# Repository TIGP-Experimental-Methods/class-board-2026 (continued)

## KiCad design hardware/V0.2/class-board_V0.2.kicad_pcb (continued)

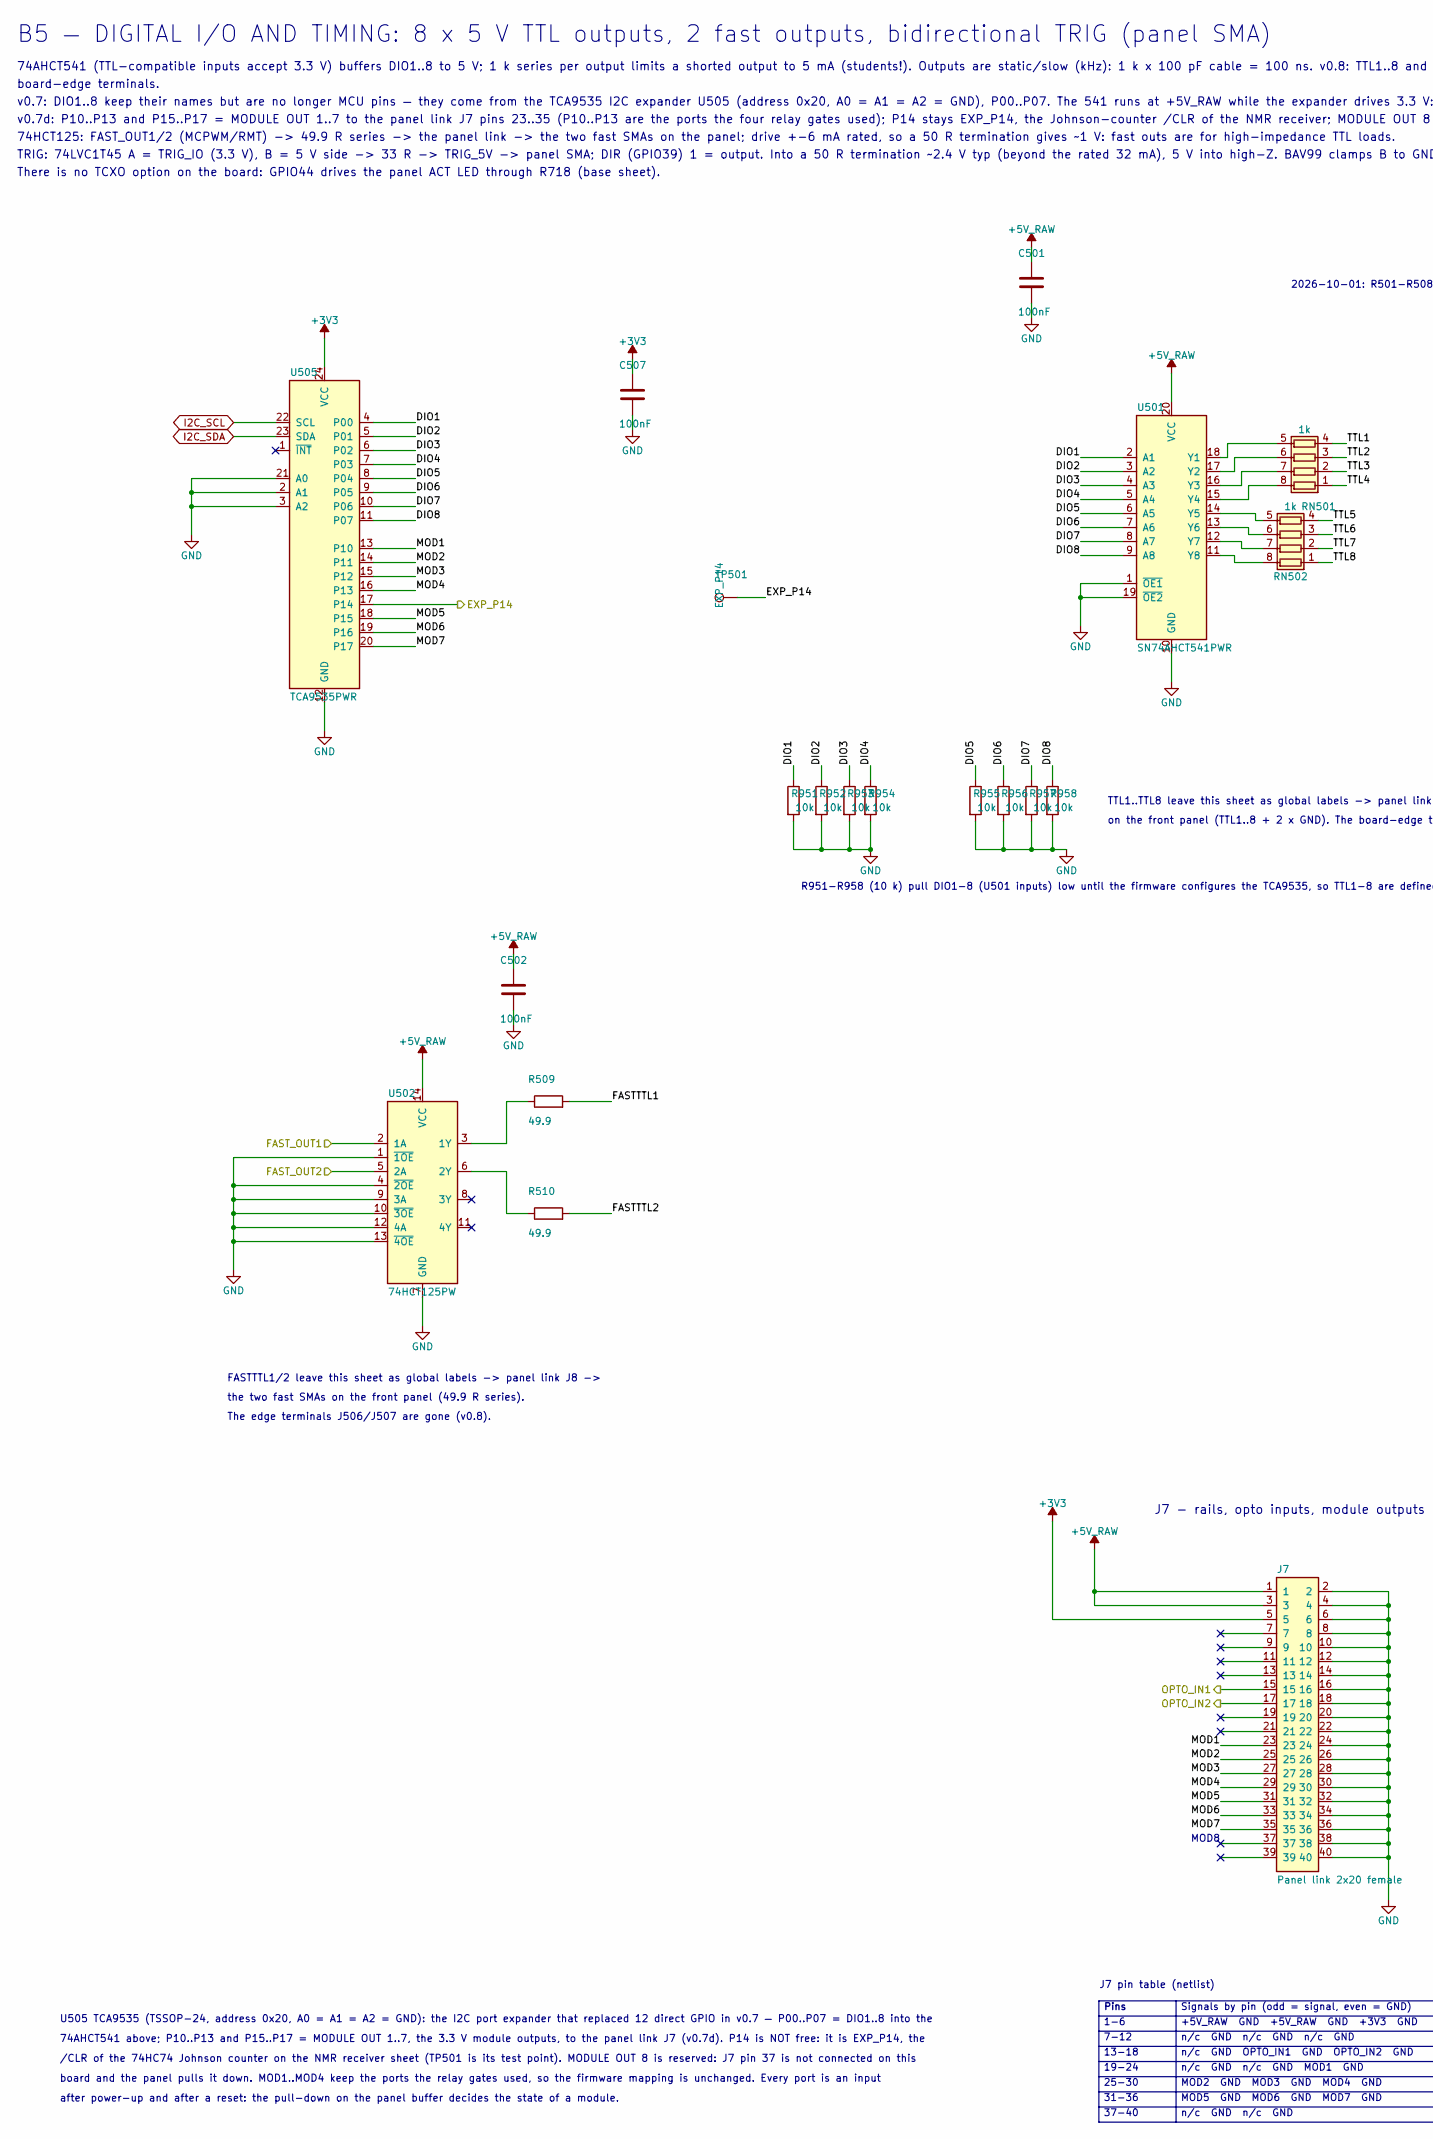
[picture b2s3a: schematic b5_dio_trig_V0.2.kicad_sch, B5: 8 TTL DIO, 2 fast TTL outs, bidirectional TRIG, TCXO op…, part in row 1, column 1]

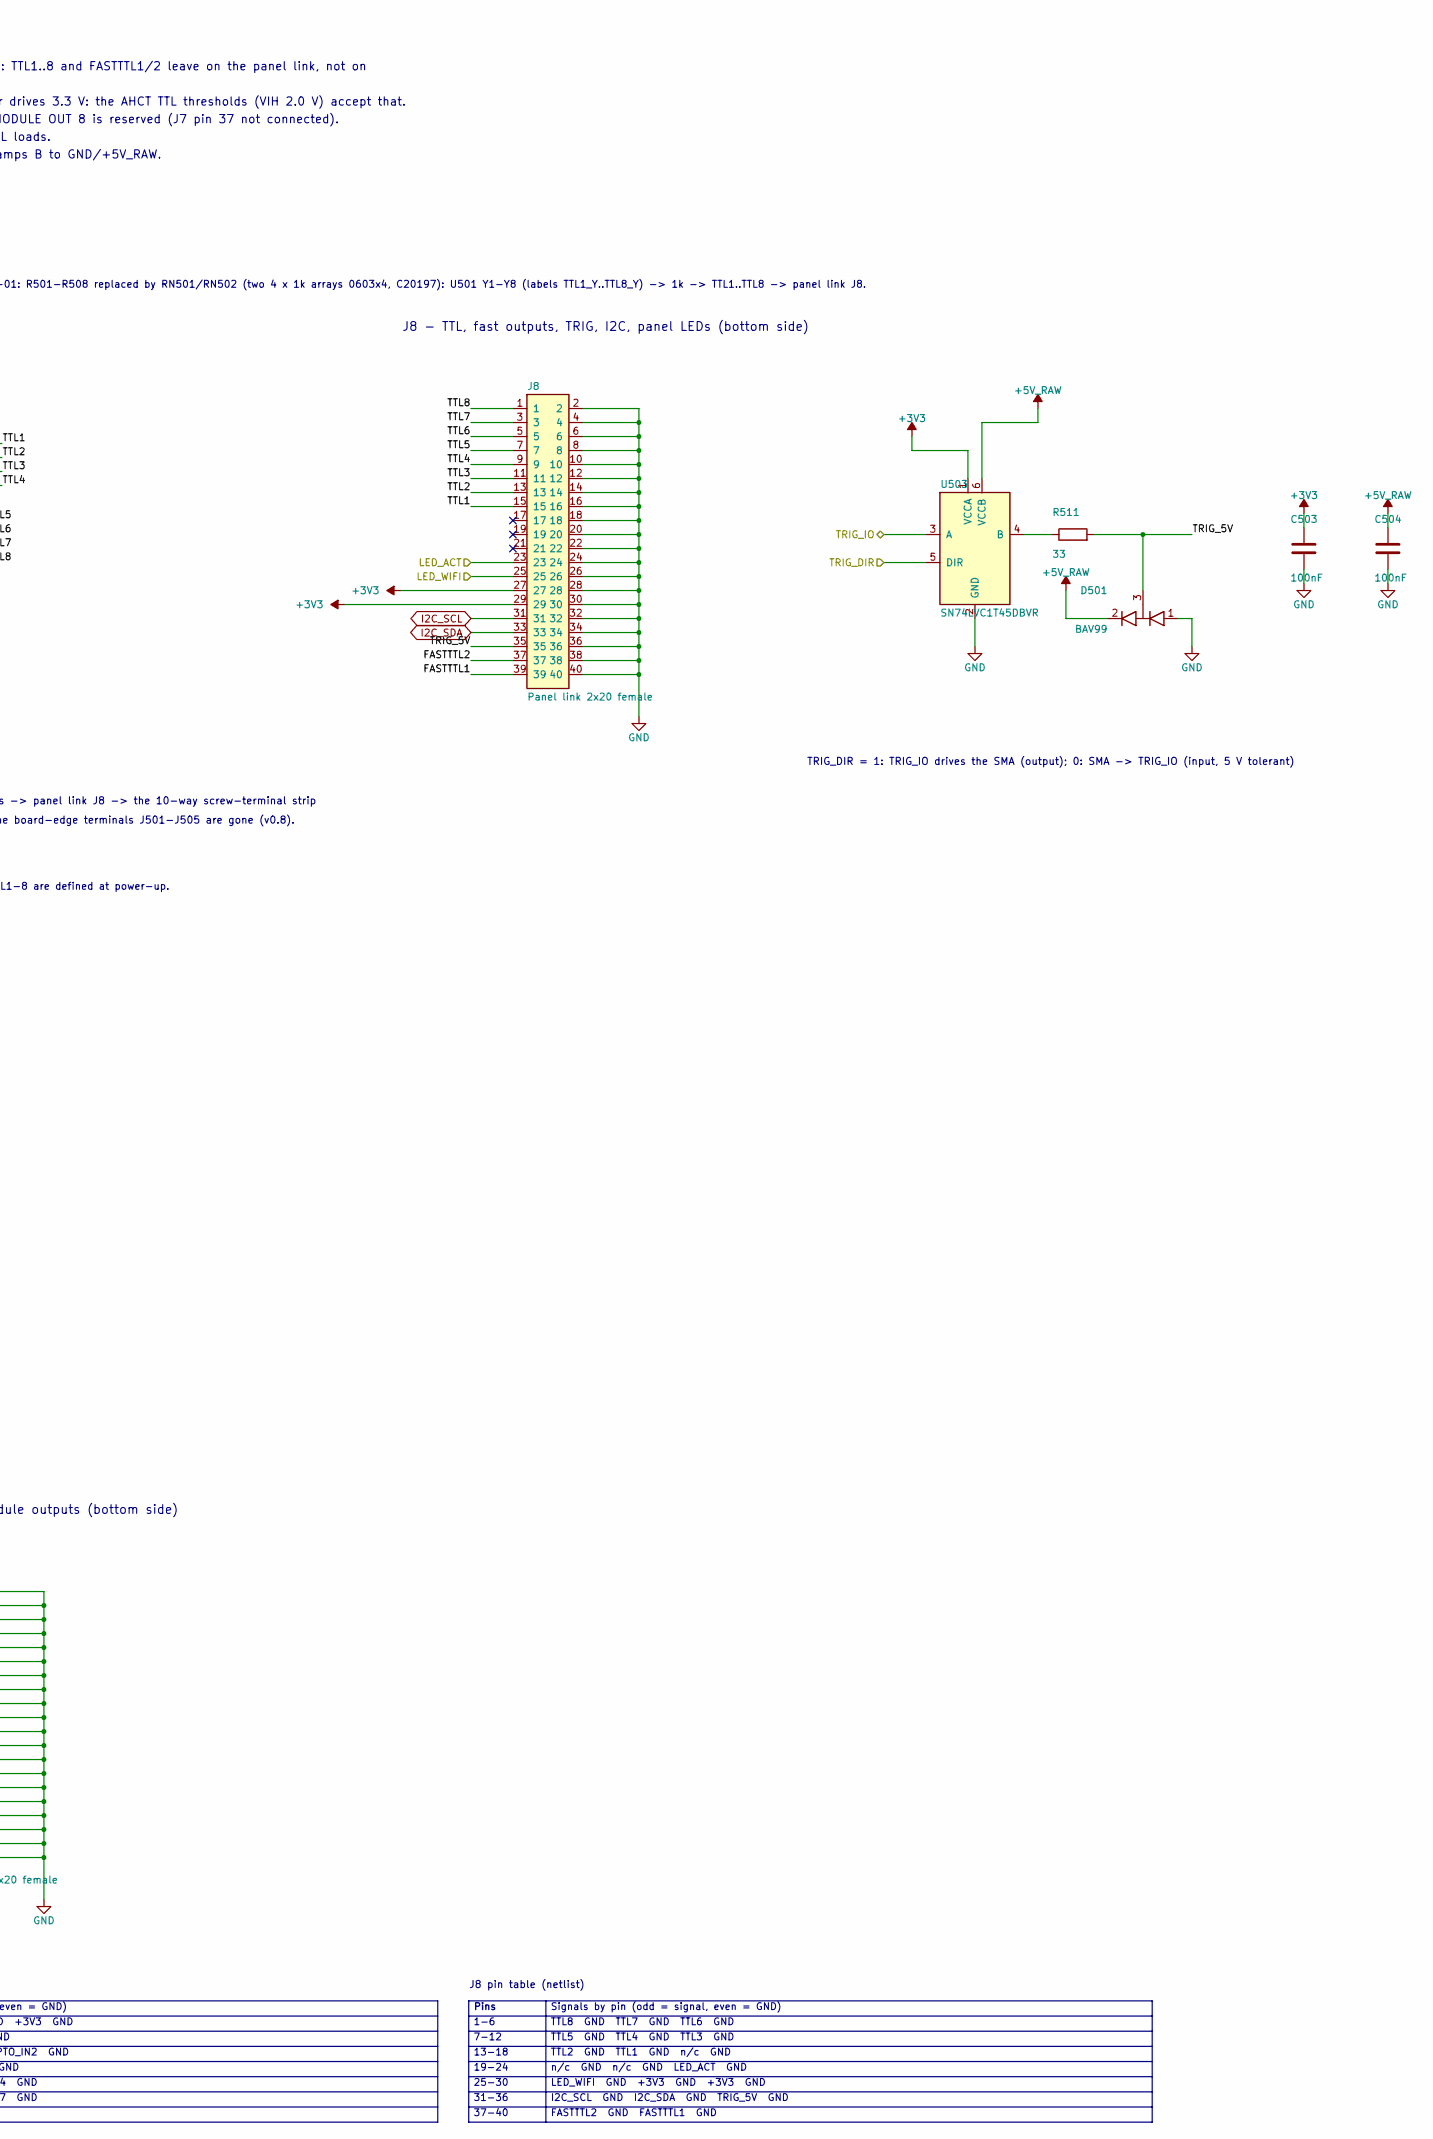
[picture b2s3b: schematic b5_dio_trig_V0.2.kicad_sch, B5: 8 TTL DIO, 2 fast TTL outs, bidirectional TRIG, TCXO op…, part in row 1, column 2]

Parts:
C501, C502, C503, C504, C507: 100nF; C_0603_1608Metric; MPN CC0603KRX7R9BB104; LCSC C14663
D501: BAV99; SOT-23-3_L2.9-W1.6-P1.90-LS2.8-BR; MPN BAV99,215; LCSC C2500
J7, J8: Panel link 2x20 female; PinSocket_2x20_P2.54mm_Vertical; MPN 2.54-2*20P (8.5 mm); LCSC C5124634
R509, R510: 49.9; R_0603_1608Metric; MPN 0603WAF499JT5E; LCSC C23185
R511: 33; R_0603_1608Metric; MPN 0603WAF330JT5E; LCSC C23140
R951, R952, R953, R954, R955, R956, R957, R958: 10k; R_0603_1608Metric; LCSC C25804
RN501, RN502: 1k; R_Array_Convex_4x0603; LCSC C20197
TP501: EXP_P14; TestPoint_Pad_D1.5mm
U501: SN74AHCT541PWR; TSSOP-20_L6.5-W4.4-P0.65-LS6.4-BL; MPN SN74AHCT541PWR; LCSC C50989
U502: 74HCT125PW; TSSOP-14_L5.0-W4.4-P0.65-LS6.4-BL; MPN 74HCT125PW,118; LCSC C131316
U503: SN74LVC1T45DBVR; SOT-23-6_L2.9-W1.6-P0.95-LS2.8-BR; MPN SN74LVC1T45DBVR; LCSC C7843
U505: TCA9535PWR; TSSOP-24_L7.8-W4.4-P0.65-LS6.4-BL; MPN TCA9535PWR; LCSC C22396388

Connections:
+3V3: C503.1, C507.1, J7.5, J8.27, J8.29, U503.1 (VCCA), U505.24 (VCC); also elsewhere on the board
/b5_dio_trig/DIO1: R951.1, U501.2 (A1), U505.4 (P00)
/b5_dio_trig/DIO2: R952.1, U501.3 (A2), U505.5 (P01)
/b5_dio_trig/DIO3: R953.1, U501.4 (A3), U505.6 (P02)
/b5_dio_trig/DIO4: R954.1, U501.5 (A4), U505.7 (P03)
/b5_dio_trig/DIO5: R955.1, U501.6 (A5), U505.8 (P04)
/b5_dio_trig/DIO6: R956.1, U501.7 (A6), U505.9 (P05)
/b5_dio_trig/DIO7: R957.1, U501.8 (A7), U505.10 (P06)
/b5_dio_trig/DIO8: R958.1, U501.9 (A8), U505.11 (P07)
/b5_dio_trig/EXP_P14: TP501.1 (1_1), U505.17 (P14); also elsewhere on the board
/b5_dio_trig/FASTTTL1: J8.39, R509.2
/b5_dio_trig/FASTTTL2: J8.37, R510.2
/b5_dio_trig/FAST_OUT1: U502.2 (1A); also elsewhere on the board
/b5_dio_trig/FAST_OUT2: U502.5 (2A); also elsewhere on the board
/b5_dio_trig/LED_ACT: J8.23; also elsewhere on the board
/b5_dio_trig/LED_WIFI: J8.25; also elsewhere on the board
/b5_dio_trig/MOD1: J7.23, U505.13 (P10)
/b5_dio_trig/MOD2: J7.25, U505.14 (P11)
/b5_dio_trig/MOD3: J7.27, U505.15 (P12)
/b5_dio_trig/MOD4: J7.29, U505.16 (P13)
/b5_dio_trig/MOD5: J7.31, U505.18 (P15)
/b5_dio_trig/MOD6: J7.33, U505.19 (P16)
/b5_dio_trig/MOD7: J7.35, U505.20 (P17)
/b5_dio_trig/OPTO_IN1: J7.15; also elsewhere on the board
/b5_dio_trig/OPTO_IN2: J7.17; also elsewhere on the board
/b5_dio_trig/TRIG_5V: D501.3 (COM), J8.35, R511.2
/b5_dio_trig/TRIG_DIR: U503.5 (DIR); also elsewhere on the board
/b5_dio_trig/TRIG_IO: U503.3 (A); also elsewhere on the board
/b5_dio_trig/TTL1: J8.15, RN501.4 (R4.1)
/b5_dio_trig/TTL2: J8.13, RN501.3 (R3.1)
/b5_dio_trig/TTL3: J8.11, RN501.2 (R2.1)
/b5_dio_trig/TTL4: J8.9, RN501.1 (R1.1)
/b5_dio_trig/TTL5: J8.7, RN502.4 (R4.1)
/b5_dio_trig/TTL6: J8.5, RN502.3 (R3.1)
/b5_dio_trig/TTL7: J8.3, RN502.2 (R2.1)
/b5_dio_trig/TTL8: J8.1, RN502.1 (R1.1)
GND: C501.2, C502.2, C503.2, C504.2, C507.2, D501.1 (A1), J7.2, J7.4, J7.6, J7.8, J7.10, J7.12, J7.14, J7.16, J7.18, J7.20, J7.22, J7.24, J7.26, J7.28, J7.30, J7.32, J7.34, J7.36, J7.38, J7.40, J8.2, J8.4, J8.6, J8.8, J8.10, J8.12, J8.14, J8.16, J8.18, J8.20, J8.22, J8.24, J8.26, J8.28, J8.30, J8.32, J8.34, J8.36, J8.38, J8.40, R951.2, R952.2, R953.2, R954.2, R955.2, R956.2, R957.2, R958.2, U501.1 (~OE1), U501.10 (GND), U501.19 (~OE2), U502.1 (~1OE), U502.4 (~2OE), U502.7 (GND), U502.9 (3A), U502.10 (~3OE), U502.12 (4A), U502.13 (~4OE), U503.2 (GND), U505.2 (A1), U505.3 (A2), U505.12 (GND), U505.21 (A0); also elsewhere on the board
I2C_SCL: J8.31, U505.22 (SCL); also elsewhere on the board
I2C_SDA: J8.33, U505.23 (SDA); also elsewhere on the board
unnamed: RN501.8 (R1.2), U501.15 (Y4)
unnamed: RN501.7 (R2.2), U501.16 (Y3)
unnamed: RN501.6 (R3.2), U501.17 (Y2)
unnamed: RN501.5 (R4.2), U501.18 (Y1)
unnamed: RN502.8 (R1.2), U501.11 (Y8)
unnamed: RN502.7 (R2.2), U501.12 (Y7)
unnamed: RN502.6 (R3.2), U501.13 (Y6)
unnamed: RN502.5 (R4.2), U501.14 (Y5)
unnamed: R509.1, U502.3 (1Y)
unnamed: R510.1, U502.6 (2Y)
unnamed: R511.1, U503.4 (B)

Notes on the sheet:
U505 TCA9535 (TSSOP-24, address 0x20, A0 = A1 = A2 = GND): the I2C port expander that replaced 12 direct GPIO in v0.7 — P00..P07 = DIO1..8 into the
v0.7: DIO1..8 keep their names but are no longer MCU pins — they come from the TCA9535 I2C expander U505 (address 0x20, A0 = A1 = A2 = GND), P00..P07. The 541 runs at +5V_RAW while the expander drives 3.3 V: the AHCT TTL thresholds (VIH 2.0 V) accept that.
after power-up and after a reset: the pull-down on the panel buffer decides the state of a module.
Pins
board-edge terminals.
25-30
2026-10-01: R501-R508 replaced by RN501/RN502 (two 4 x 1k arrays 0603x4, C20197): U501 Y1-Y8 (labels TTL1_Y..TTL8_Y) -> 1k -> TTL1..TTL8 -> panel link J8.
1-6
The edge terminals J506/J507 are gone (v0.8).
19-24
13-18
74HCT125: FAST_OUT1/2 (MCPWM/RMT) -> 49.9 R series -> the panel link -> the two fast SMAs on the panel; drive +-6 mA rated, so a 50 R termination gives ~1 V: fast outs are for high-impedance TTL loads.
TRIG: 74LVC1T45 A = TRIG_IO (3.3 V), B = 5 V side -> 33 R -> TRIG_5V -> panel SMA; DIR (GPIO39) 1 = output. Into a 50 R termination ~2.4 V typ (beyond the rated 32 mA), 5 V into high-Z. BAV99 clamps B to GND/+5V_RAW.
the two fast SMAs on the front panel (49.9 R series).
7-12
board and the panel pulls it down. MOD1..MOD4 keep the ports the relay gates used, so the firmware mapping is unchanged. Every port is an input
MOD8
on the front panel (TTL1..8 + 2 x GND). The board-edge terminals J501-J505 are gone (v0.8).
TRIG_DIR = 1: TRIG_IO drives the SMA (output); 0: SMA -> TRIG_IO (input, 5 V tolerant)
31-36
74AHCT541 (TTL-compatible inputs accept 3.3 V) buffers DIO1..8 to 5 V; 1 k series per output limits a shorted output to 5 mA (students!). Outputs are static/slow (kHz): 1 k x 100 pF cable = 100 ns. v0.8: TTL1..8 and FASTTTL1/2 leave on the panel link, not on
37-40
J7 pin table (netlist)
Signals by pin (odd = signal, even = GND)
+5V_RAW GND +5V_RAW GND +3V3 GND
n/c GND n/c GND n/c GND
n/c GND OPTO_IN1 GND OPTO_IN2 GND
n/c GND n/c GND MOD1 GND
MOD2 GND MOD3 GND MOD4 GND
MOD5 GND MOD6 GND MOD7 GND
n/c GND n/c GND
J8 pin table (netlist)
TTL8 GND TTL7 GND TTL6 GND
TTL5 GND TTL4 GND TTL3 GND
TTL2 GND TTL1 GND n/c GND
n/c GND n/c GND LED_ACT GND
LED_WIFI GND +3V3 GND +3V3 GND
I2C_SCL GND I2C_SDA GND TRIG_5V GND
FASTTTL2 GND FASTTTL1 GND
J7 - rails, opto inputs, module outputs (bottom side)

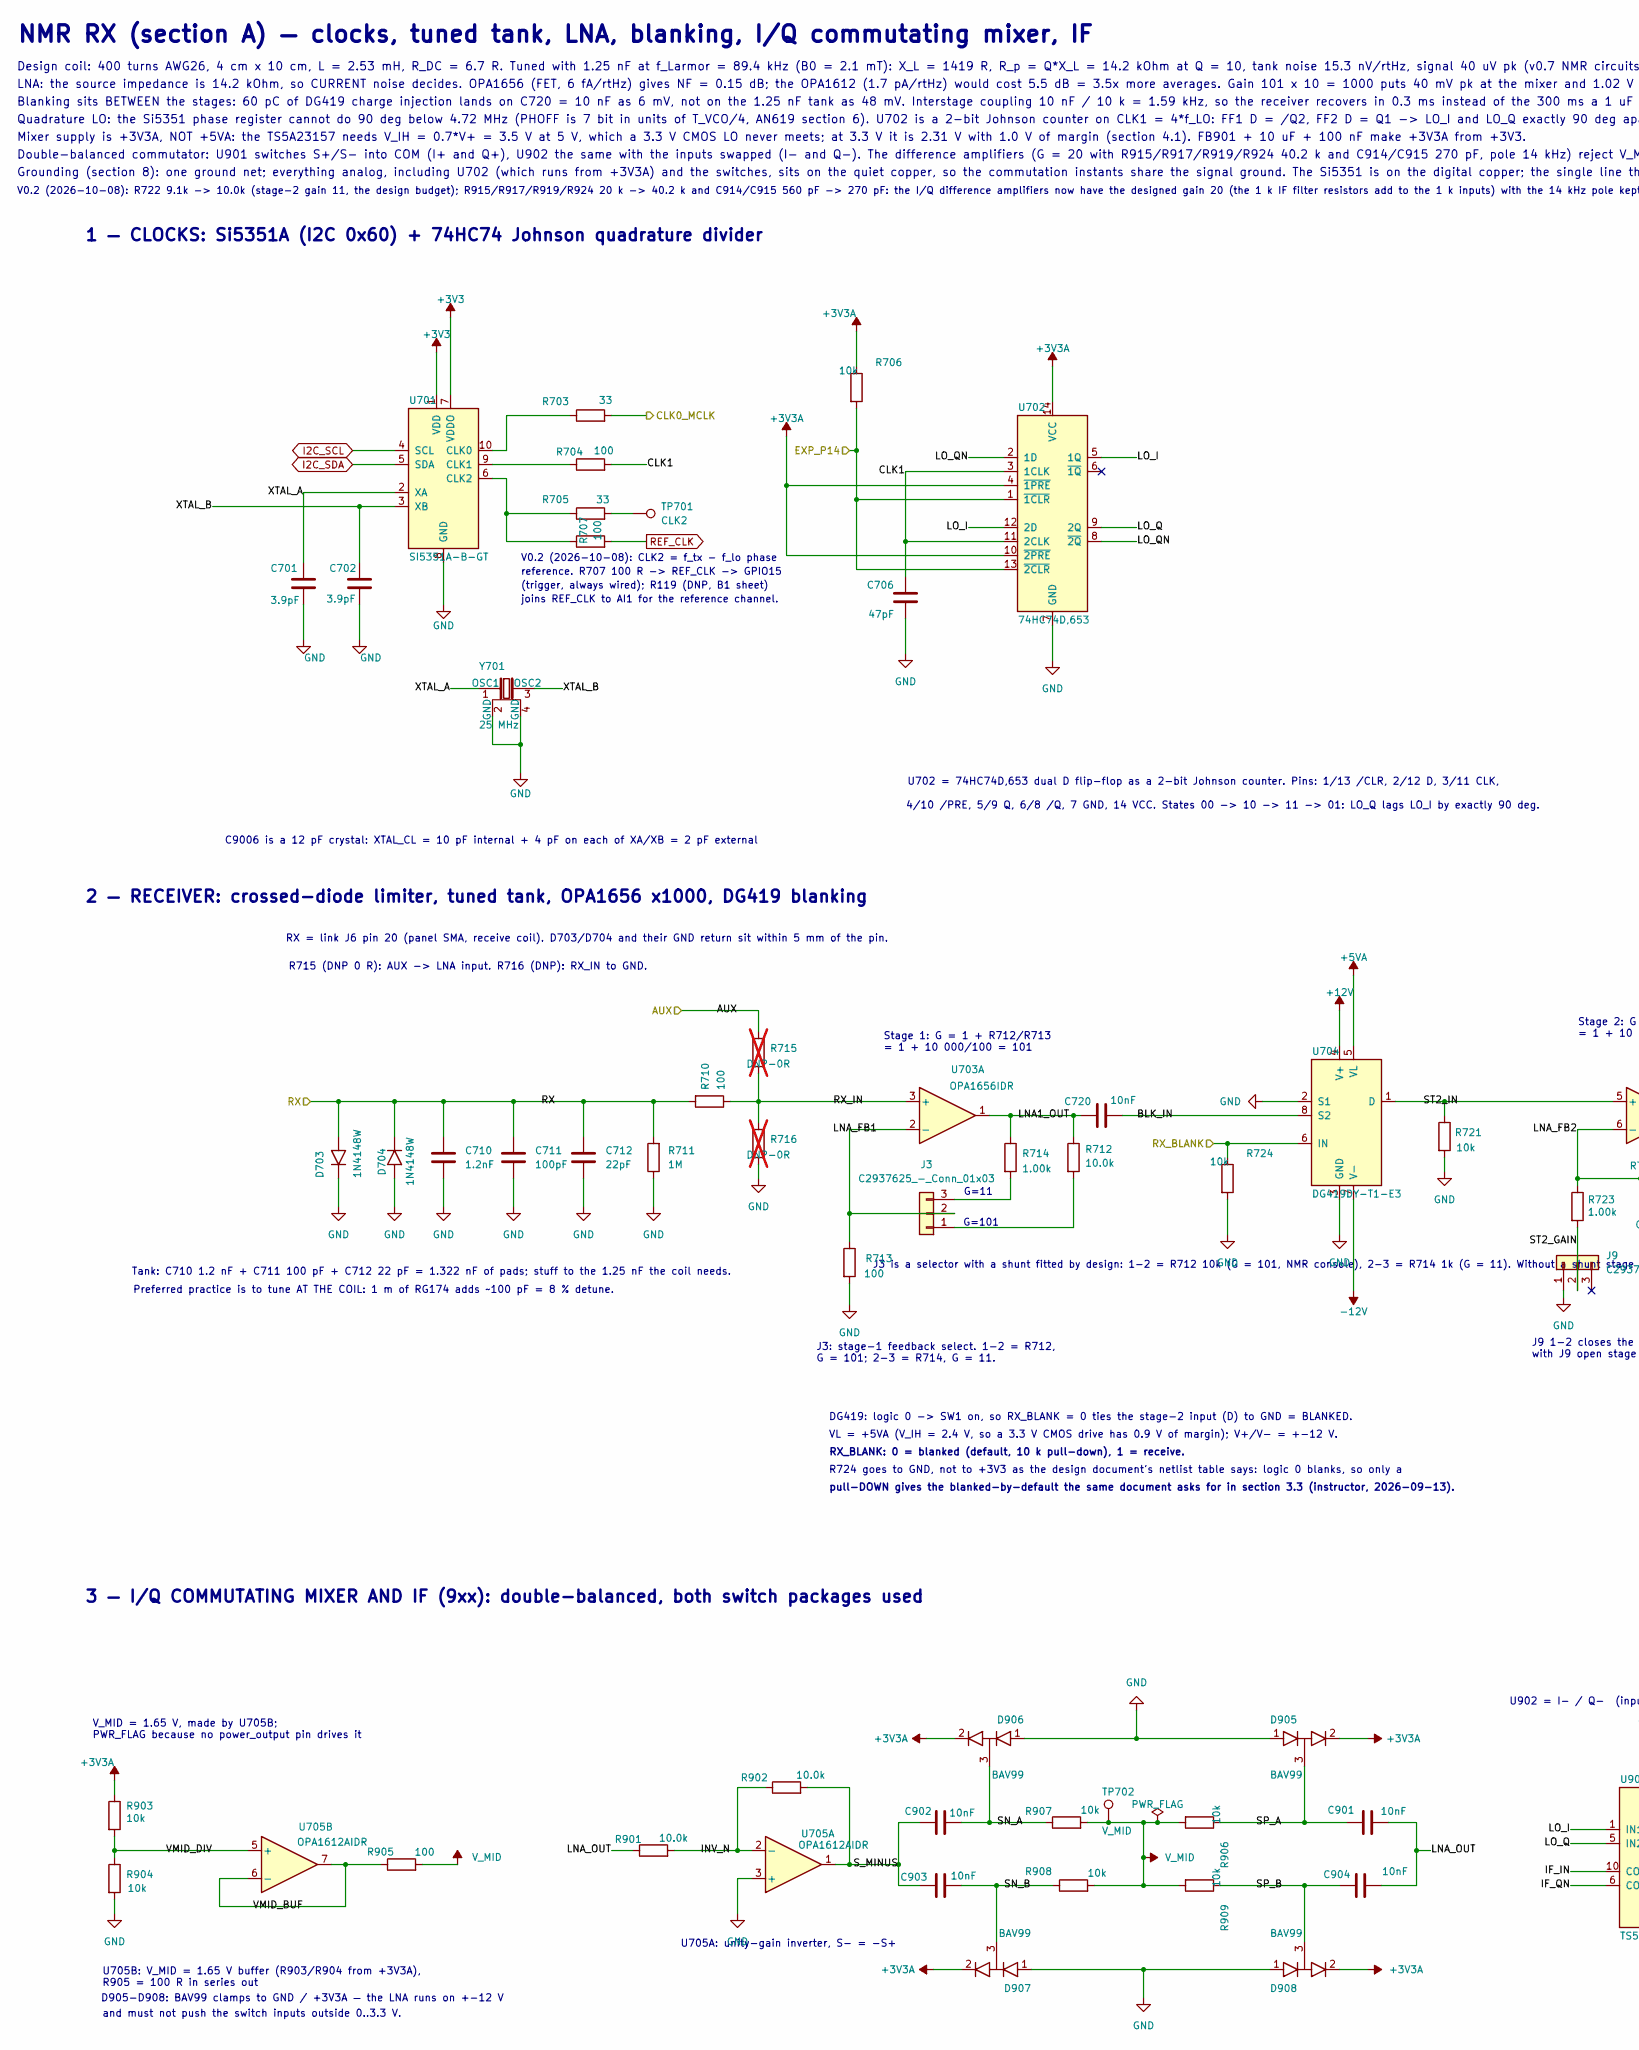
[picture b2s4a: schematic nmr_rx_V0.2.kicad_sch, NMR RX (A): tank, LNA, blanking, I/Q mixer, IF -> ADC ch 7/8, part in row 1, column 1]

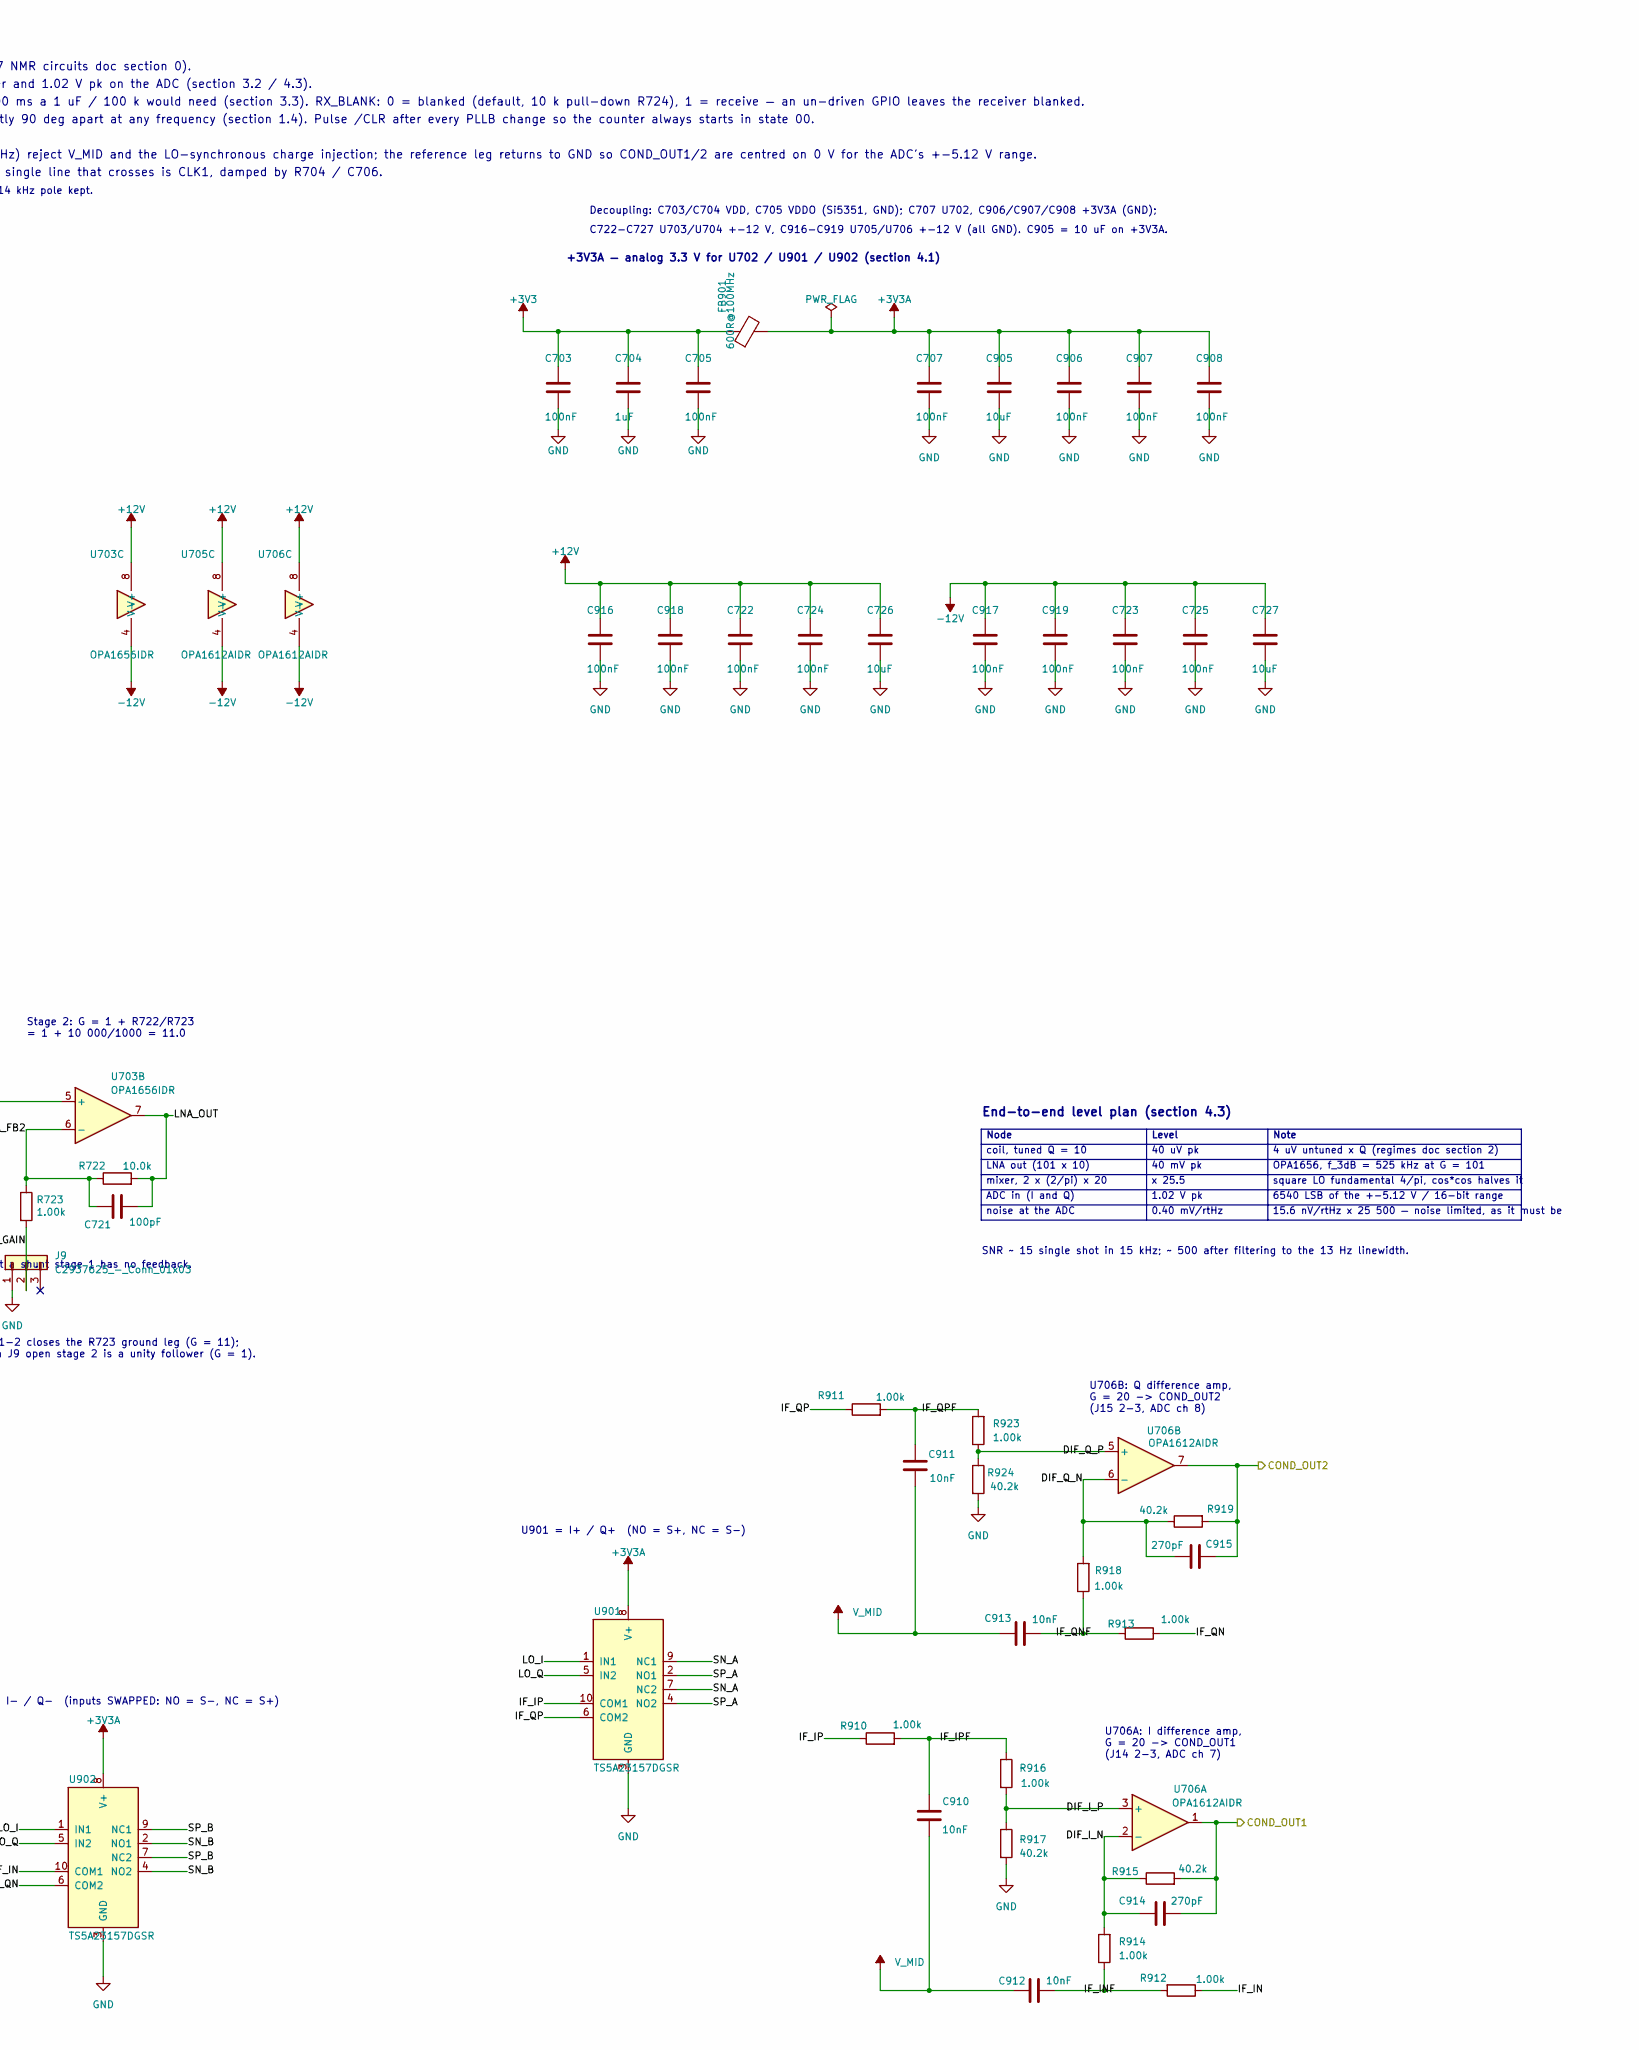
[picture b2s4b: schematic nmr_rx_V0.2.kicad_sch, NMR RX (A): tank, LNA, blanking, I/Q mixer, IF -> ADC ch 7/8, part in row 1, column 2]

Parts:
C701, C702: 3.9pF; C_0603_1608Metric; MPN CC0603BRNPO9BN3R9; LCSC C519107
C703, C705, C707, C722, C723, C724, C725, C906, C907, C908, C916, C917, C918, C919: 100nF; C_0603_1608Metric; MPN CC0603KRX7R9BB104; LCSC C14663
C704: 1uF; C_0603_1608Metric; MPN CL10A105KB8NNNC; LCSC C15849
C706: 47pF; C_0603_1608Metric; MPN CL10C470JB8NNNC; LCSC C1671
C710: 1.2nF; C_0603_1608Metric; MPN CC0603JRNPO9BN122; LCSC C576816
C711, C721: 100pF; C_0603_1608Metric; MPN CL10C101JB8NNNC; LCSC C14858
C712: 22pF; C_0603_1608Metric; MPN CL10C220JB8NNNC; LCSC C1653
C720, C901, C902, C903, C904, C910, C911, C912, C913: 10nF; C_0603_1608Metric; MPN CL10B103KB8NNNC; LCSC C1589
C726, C727, C905: 10uF; C_0805_2012Metric; MPN CL21A106KAYNNNE; LCSC C15850
C914, C915: 270pF; C_0603_1608Metric; MPN CC0603JRNPO9BN271; LCSC C107046
D703, D704: 1N4148W; SOD-123F_L2.7-W1.6-LS3.8-RD; MPN 1N4148W; LCSC C81598
D905, D906, D907, D908: BAV99; SOT-23-3_L2.9-W1.6-P1.90-LS2.8-BR; MPN BAV99,215; LCSC C2500
FB901: 600R@100MHz; L0603; MPN GZ1608D601TF; LCSC C1002
J3, J9: C2937625_-_Conn_01x03; C2937625-HDR-TH_3P-P2.54-V-M; LCSC C2937625
R703, R705: 33; R_0603_1608Metric; MPN 0603WAF330JT5E; LCSC C23140
R704, R710, R713, R905: 100; R_0603_1608Metric; MPN 0603WAF1000T5E; LCSC C22775
R706, R721, R724, R903, R904, R906, R907, R908, R909: 10k; R_0603_1608Metric; MPN 0603WAF1002T5E; LCSC C25804
R707: 100; R_0603_1608Metric; MPN 0603WAF1000T5E; JLC_CLASS Basic
R711: 1M; R_0603_1608Metric; MPN 0603WAF1004T5E; LCSC C22935
R712, R722, R901, R902: 10.0k; R_0603_1608Metric; MPN RT0603BRD0710KL; LCSC C95204
R714, R723, R910, R911, R912, R913, R914, R916, R918, R923: 1.00k; R_0603_1608Metric; MPN RT0603BRD071KL; LCSC C110776
R715, R716: DNP-0R; R_0805_2012Metric_Pad1.20x1.40mm_HandSolder; LCSC C17477; not fitted
R915, R917, R919, R924: 40.2k; R_0603_1608Metric; MPN 0603WAF4022T5E; LCSC C12447
TP701: CLK2; TestPoint_Pad_D1.5mm
TP702: V_MID; TestPoint_Pad_D1.5mm
U701: SI5351A-B-GT; MSOP-10_L3.0-W3.0-P0.50-LS5.0-BL; MPN SI5351A-B-GT; LCSC C504891
U702: 74HC74D,653; SOIC-14_L8.7-W3.9-P1.27-LS6.0-BL; MPN 74HC74D,653; LCSC C27597
U703: OPA1656IDR; SOIC-8_L5.0-W4.0-P1.27-LS6.0-BL; MPN OPA1656IDR; LCSC C1849431
U704: DG419DY-T1-E3; SOIC-8_L4.9-W3.9-P1.27-LS6.0-BL; MPN DG419DY-T1-E3; LCSC C6581
U705, U706: OPA1612AIDR; SOIC-8_L5.0-W4.0-P1.27-LS6.0-BL; MPN OPA1612AIDR; LCSC C94590
U901, U902: TS5A23157DGSR; MSOP-10_L3.0-W3.0-P0.50-LS5.0-BL; MPN TS5A23157DGSR; LCSC C11133
Y701: 25 MHz; CRYSTAL-SMD_4P-L3.2-W2.5-BL; MPN X322525MOB4SI; LCSC C9006

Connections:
+3V3: C703.1, C704.1, C705.1, FB901.1, U701.1 (VDD), U701.7 (VDDO); also elsewhere on the board
+5VA: U704.5 (VL); also elsewhere on the board
/b1_inputs/AUX: R715.2; also elsewhere on the board
/b1_inputs/COND_OUT1: C914.2, R915.2, U706.1; also elsewhere on the board
/b1_inputs/COND_OUT2: C915.2, R919.2, U706.7; also elsewhere on the board
/b1_inputs/RX: C710.2, C711.2, C712.2, D703.2 (A), D704.1 (K), R710.2, R711.2; also elsewhere on the board
/b5_dio_trig/EXP_P14: R706.2, U702.1 (~1CLR), U702.13 (~2CLR); also elsewhere on the board
/base_mcu/RX_BLANK: R724.1, U704.6 (IN); also elsewhere on the board
/nmr_rx/BLK_IN: C720.2, U704.8 (S2)
/nmr_rx/CLK0_MCLK: R703.2; also elsewhere on the board
/nmr_rx/CLK1: C706.1, R704.2, U702.3 (1CLK), U702.11 (2CLK)
/nmr_rx/DIF_I_N: C914.1, R914.2, R915.1, U706.2 (-)
/nmr_rx/DIF_I_P: R916.2, R917.1, U706.3 (+)
/nmr_rx/DIF_Q_N: C915.1, R918.2, R919.1, U706.6 (-)
/nmr_rx/DIF_Q_P: R923.1, R924.1, U706.5 (+)
/nmr_rx/IF_IN: R912.1, U902.10 (COM1)
/nmr_rx/IF_INF: C912.1, R912.2, R914.1
/nmr_rx/IF_IP: R910.1, U901.10 (COM1)
/nmr_rx/IF_IPF: C910.2, R910.2, R916.1
/nmr_rx/IF_QN: R913.1, U902.6 (COM2)
/nmr_rx/IF_QNF: C913.1, R913.2, R918.1
/nmr_rx/IF_QP: R911.1, U901.6 (COM2)
/nmr_rx/IF_QPF: C911.2, R911.2, R923.2
/nmr_rx/INV_N: R901.2, R902.1, U705.2 (-)
/nmr_rx/LNA1_OUT: C720.1, R712.1, R714.1, U703.1
/nmr_rx/LNA_FB1: J3.2, R713.1, U703.2 (-)
/nmr_rx/LNA_FB2: C721.1, R722.1, R723.1, U703.6 (-)
/nmr_rx/LNA_OUT: C721.2, C901.1, C904.1, R722.2, R901.1, U703.7
/nmr_rx/LO_I: U702.5 (1Q), U702.12 (2D), U901.1 (IN1), U902.1 (IN1)
/nmr_rx/LO_Q: U702.9 (2Q), U901.5 (IN2), U902.5 (IN2)
/nmr_rx/LO_QN: U702.2 (1D), U702.8 (~2Q)
/nmr_rx/RX_IN: R710.1, R715.1, R716.2, U703.3 (+)
/nmr_rx/SN_A: C902.2, D906.3 (COM), R907.1, U901.7 (NC2), U901.9 (NC1)
/nmr_rx/SN_B: C903.2, D907.3 (COM), R908.1, U902.2 (NO1), U902.4 (NO2)
/nmr_rx/SP_A: C901.2, D905.3 (COM), R906.1, U901.2 (NO1), U901.4 (NO2)
/nmr_rx/SP_B: C904.2, D908.3 (COM), R909.1, U902.7 (NC2), U902.9 (NC1)
/nmr_rx/ST2_GAIN: J9.2, R723.2
/nmr_rx/ST2_IN: R721.1, U703.5 (+), U704.1 (D)
/nmr_rx/S_MINUS: C902.1, C903.1, R902.2, U705.1
/nmr_rx/VMID_BUF: R905.1, U705.6 (-), U705.7
/nmr_rx/VMID_DIV: R903.2, R904.1, U705.5 (+)
/nmr_rx/XTAL_A: C701.1, U701.2 (XA), Y701.1 (OSC1)
/nmr_rx/XTAL_B: C702.1, U701.3 (XB), Y701.3 (OSC2)
GND: C701.2, C702.2, C703.2, C704.2, C705.2, C706.2, C707.2, C710.1, C711.1, C712.1, C722.2, C723.2, C724.2, C725.2, C726.2, C727.2, C905.2, C906.2, C907.2, C908.2, C916.2, C917.2, C918.2, C919.2, D703.1 (K), D704.2 (A), D905.1 (A1), D906.1 (A1), D907.1 (A1), D908.1 (A1), J9.1, R711.1, R713.2, R716.1, R721.2, R724.2, R904.2, R917.2, R924.2, U701.8 (GND), U702.7 (GND), U704.2 (S1), U704.3 (GND), U705.3 (+), U901.3 (GND), U902.3 (GND), Y701.2 (GND), Y701.4 (GND); also elsewhere on the board
I2C_SCL: U701.4 (SCL); also elsewhere on the board
I2C_SDA: U701.5 (SDA); also elsewhere on the board
unnamed: J3.1, R712.2
unnamed: J3.3, R714.2
unnamed: R705.2, TP701.1 (1_1)
unnamed: R703.1, U701.10 (CLK0)
unnamed: R704.1, U701.9 (CLK1)
unnamed: R705.1, R707.1, U701.6 (CLK2)
REF_CLK: R707.2; also elsewhere on the board

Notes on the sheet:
End-to-end level plan (section 4.3)
Node
Note
3 — I/Q COMMUTATING MIXER AND IF (9xx): double-balanced, both switch packages used
Preferred practice is to tune AT THE COIL: 1 m of RG174 adds ~100 pF = 8 % detune.
coil, tuned Q = 10
1.02 V pk
x 25.5
15.6 nV/rtHz x 25 500 — noise limited, as it must be
LNA out (101 x 10)
Blanking sits BETWEEN the stages: 60 pC of DG419 charge injection lands on C720 = 10 nF as 6 mV, not on the 1.25 nF tank as 48 mV. Interstage coupling 10 nF / 10 k = 1.59 kHz, so the receiver recovers in 0.3 ms instead of the 300 ms a 1 uF / 100 k would need (section 3.3). RX_BLANK: 0 = blanked (de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
VL = +5VA (V_IH = 2.4 V, so a 3.3 V CMOS drive has 0.9 V of margin); V+/V- = +-12 V.
V_MID = 1.65 V, made by U705B; PWR_FLAG because no power_output pin drives it
U705A: unity-gain inverter, S- = -S+
Level
Tank: C710 1.2 nF + C711 100 pF + C712 22 pF = 1.322 nF of pads; stuff to the 1.25 nF the coil needs.
Design coil: 400 turns AWG26, 4 cm x 10 cm, L = 2.53 mH, R_DC = 6.7 R. Tuned with 1.25 nF at f_Larmor = 89.4 kHz (B0 = 2.1 mT): X_L = 1419 R, R_p = Q*X_L = 14.2 kOhm at Q = 10, tank noise 15.3 nV/rtHz, signal 40 uV pk (v0.7 NMR circuits doc section 0).
RX_BLANK: 0 = blanked (default, 10 k pull-down), 1 = receive.
pull-DOWN gives the blanked-by-default the same document asks for in section 3.3 (instructor, 2026-09-13).
+3V3A — analog 3.3 V for U702 / U901 / U902 (section 4.1)
U702 = 74HC74D,653 dual D flip-flop as a 2-bit Johnson counter. Pins: 1/13 /CLR, 2/12 D, 3/11 CLK,
Stage 1: G = 1 + R712/R713 = 1 + 10 000/100 = 101
SNR ~ 15 single shot in 15 kHz; ~ 500 after filtering to the 13 Hz linewidth.
0.40 mV/rtHz
noise at the ADC
U901 = I+ / Q+ (NO = S+, NC = S-)
4/10 /PRE, 5/9 Q, 6/8 /Q, 7 GND, 14 VCC. States 00 -> 10 -> 11 -> 01: LO_Q lags LO_I by exactly 90 deg.
2 — RECEIVER: crossed-diode limiter, tuned tank, OPA1656 x1000, DG419 blanking
C9006 is a 12 pF crystal: XTAL_CL = 10 pF internal + 4 pF on each of XA/XB = 2 pF external
Quadrature LO: the Si5351 phase register cannot do 90 deg below 4.72 MHz (PHOFF is 7 bit in units of T_VCO/4, AN619 section 6). U702 is a 2-bit Johnson counter on CLK1 = 4*f_LO: FF1 D = /Q2, FF2 D = Q1 -> LO_I and LO_Q exactly 90 deg apart at any frequency (section 1.4). Pulse /CLR after every PLLB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
G=101
4 uV untuned x Q (regimes doc section 2)
OPA1656, f_3dB = 525 kHz at G = 101
square LO fundamental 4/pi, cos*cos halves it
1 — CLOCKS: Si5351A (I2C 0x60) + 74HC74 Johnson quadrature divider
and must not push the switch inputs outside 0..3.3 V.
U705B: V_MID = 1.65 V buffer (R903/R904 from +3V3A), R905 = 100 R in series out
6540 LSB of the +-5.12 V / 16-bit range
NMR RX (section A) — clocks, tuned tank, LNA, blanking, I/Q commutating mixer, IF
mixer, 2 x (2/pi) x 20
